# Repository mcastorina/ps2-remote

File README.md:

# ps2-remote

## What is it?
Make my Playstation 2 reset button be controlled remotely. It uses an
infrared sensor (for the remote part), and a single input MUX (for
simulating a button press).

## Motivation
I don't want to get up to turn on and off my Playstation 2.

## Dependencies
Arduino Libraries:

* [Arduino-IRremote](https://github.com/shirriff/Arduino-IRremote)

## Status
- [x] Working prototype on breadboard
- [x] Transfer off of Arduino board
- [x] Design PCB
- [x] Order PCB
- [x] Done!

## Future Goals
This project converts any button into an IR controlled button, however
it requires soldering and electrical knowledge to do so. A future goal
is to simplify the process to allow anyone to convert the buttons.

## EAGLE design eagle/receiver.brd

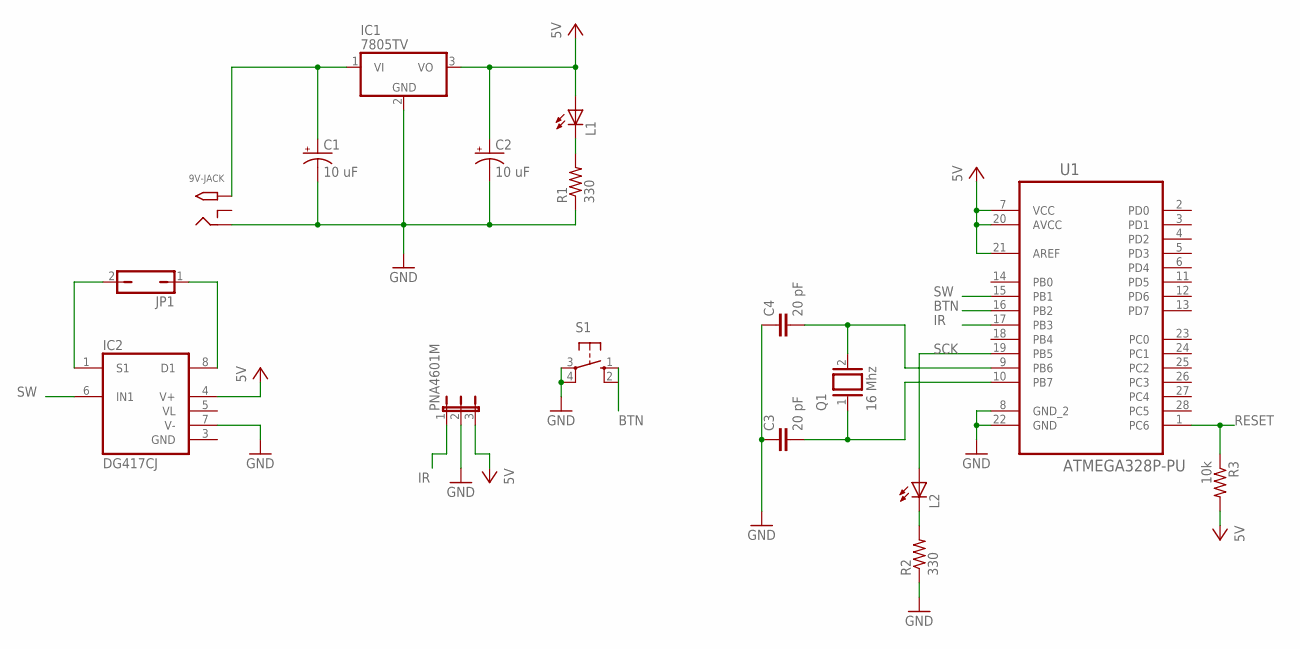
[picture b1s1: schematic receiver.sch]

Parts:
9V-JACK: 9V Input; PJ-102A
C1, C2: 10 uF; B45181B
C3, C4: 20 pF; C050-025X075
IC1: 7805TV; TO220V
IC2: DG417CJ; DIL08
JP1: JP1Q; JP1
L1, L2: LED3MM
PNA4601M: JP2E; JP2
Q1: 16 Mhz; QS
R1, R2: 330; RES400MIL
R3: 10k; RES400MIL
S1: B3F-1052; B3F-10XX
U1: ATMEGA328P-PU; DIP254P762X457-28

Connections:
5V: C2.+, IC1.3 (VO), IC2.4 (V+), L1.A, PNA4601M.3, R3.2, U1.7 (VCC), U1.20 (AVCC), U1.21 (AREF)
BTN: S1.1 (S), U1.16 (PB2)
GND: 9V-JACK.RING, C1.-, C2.-, C3.1, C4.1, IC1.2 (GND), IC2.3 (GND), IC2.7 (V-), PNA4601M.2, R1.1, R2.1, S1.3, S1.4 (P1), U1.8 (GND_2), U1.22 (GND)
IR: PNA4601M.1, U1.17 (PB3)
unnamed: L1.K (C), R1.2
unnamed: IC2.1 (S1), JP1.2
unnamed: C3.2, Q1.1, U1.10 (PB7)
unnamed: C4.2, Q1.2, U1.9 (PB6)
unnamed: IC2.8 (D1), JP1.1
unnamed: 9V-JACK.TIP, C1.+, IC1.1 (VI)
unnamed: L2.K (C), R2.2
RESET: R3.1, U1.1 (PC6)
SCK: L2.A, U1.19 (PB5)
SW: IC2.6 (IN1), U1.15 (PB1)
VL: IC2.5 (VL)

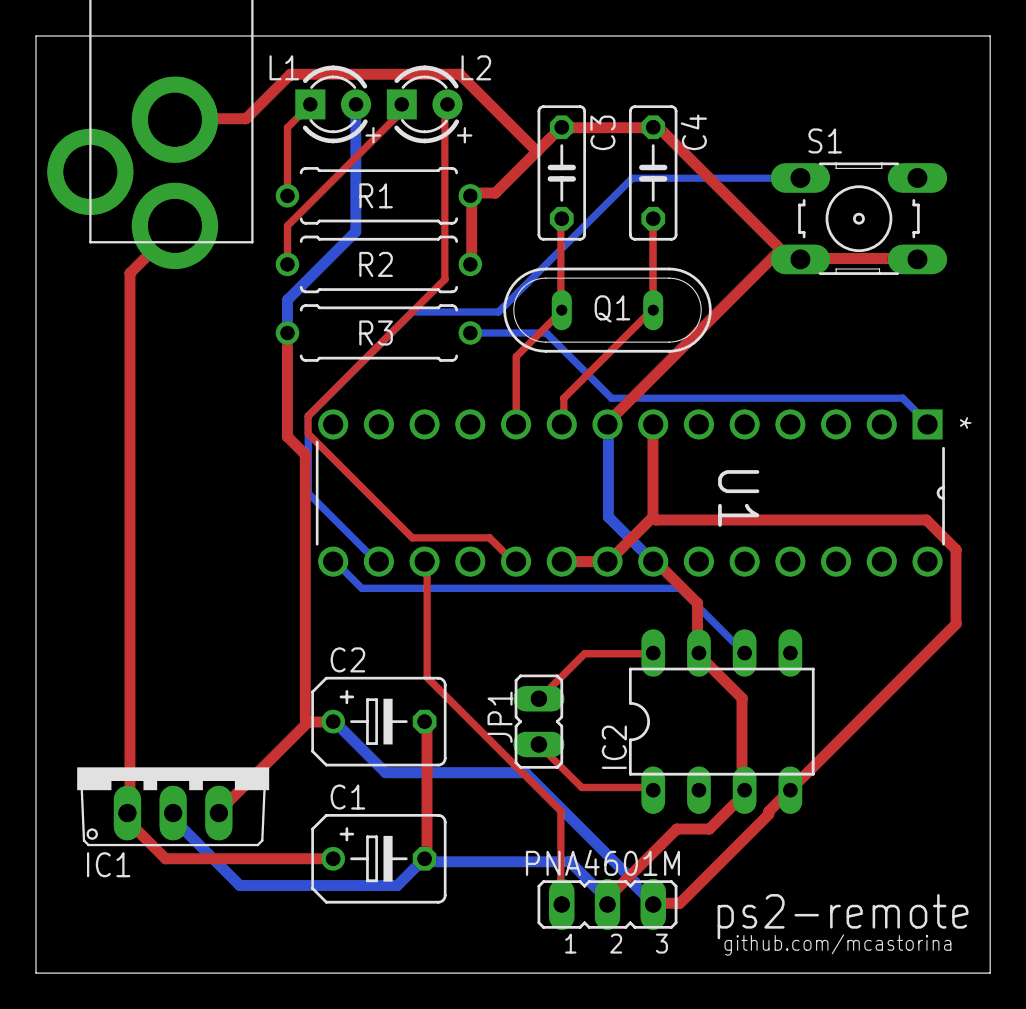
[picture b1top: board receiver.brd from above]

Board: 2 copper layers, 53.0 x 52.1 mm, 17 parts (0 on the bottom side), 14 nets.

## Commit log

2016-07-09 Added debug code, fixed EEPROM storing, and fixed compile error
    Fully tested and works on a breadboard.
2016-07-09 Simplified get_code
    Instead of using the raw data to generate a code, I changed to using the
    provided 'value' attribute. This is a more unique identifier and less
    prone to error.
2016-07-09 Fixed EEPROM reading and writing the full long value
    Previously, I was only storing half the long. I fixed this by
    typecasting to long values instead of ints.
2016-07-09 Updated to allow multiple buttons
    Each button now has a map to a function, and multiple IR codes can be
    saved.
2016-07-11 Transferred off of Arduino board
2016-07-13 Initial commit of eagle files
2016-07-13 Added tpl0401b (dpot) breakout component
2016-07-13 Finished design of PCB
2016-07-24 Added LED output for visual confirmation
2016-07-25 Refactored blinking code
2016-07-25 Fixed reversed DC power jack and finished PCB
2016-07-29 Initialized button as unpressed in setup
2016-07-29 Finished project
2016-07-31 Removed dpot from project and replaced with single input MUX
2016-07-31 Changed code to use MUX
2016-07-31 Updated README to reflect current status
2016-09-05 Installed OSHPark board and finished!
2017-07-11 Updated README.md to properly display
2022-08-20 Add oshpark board image
2022-08-20 Add datasheets
